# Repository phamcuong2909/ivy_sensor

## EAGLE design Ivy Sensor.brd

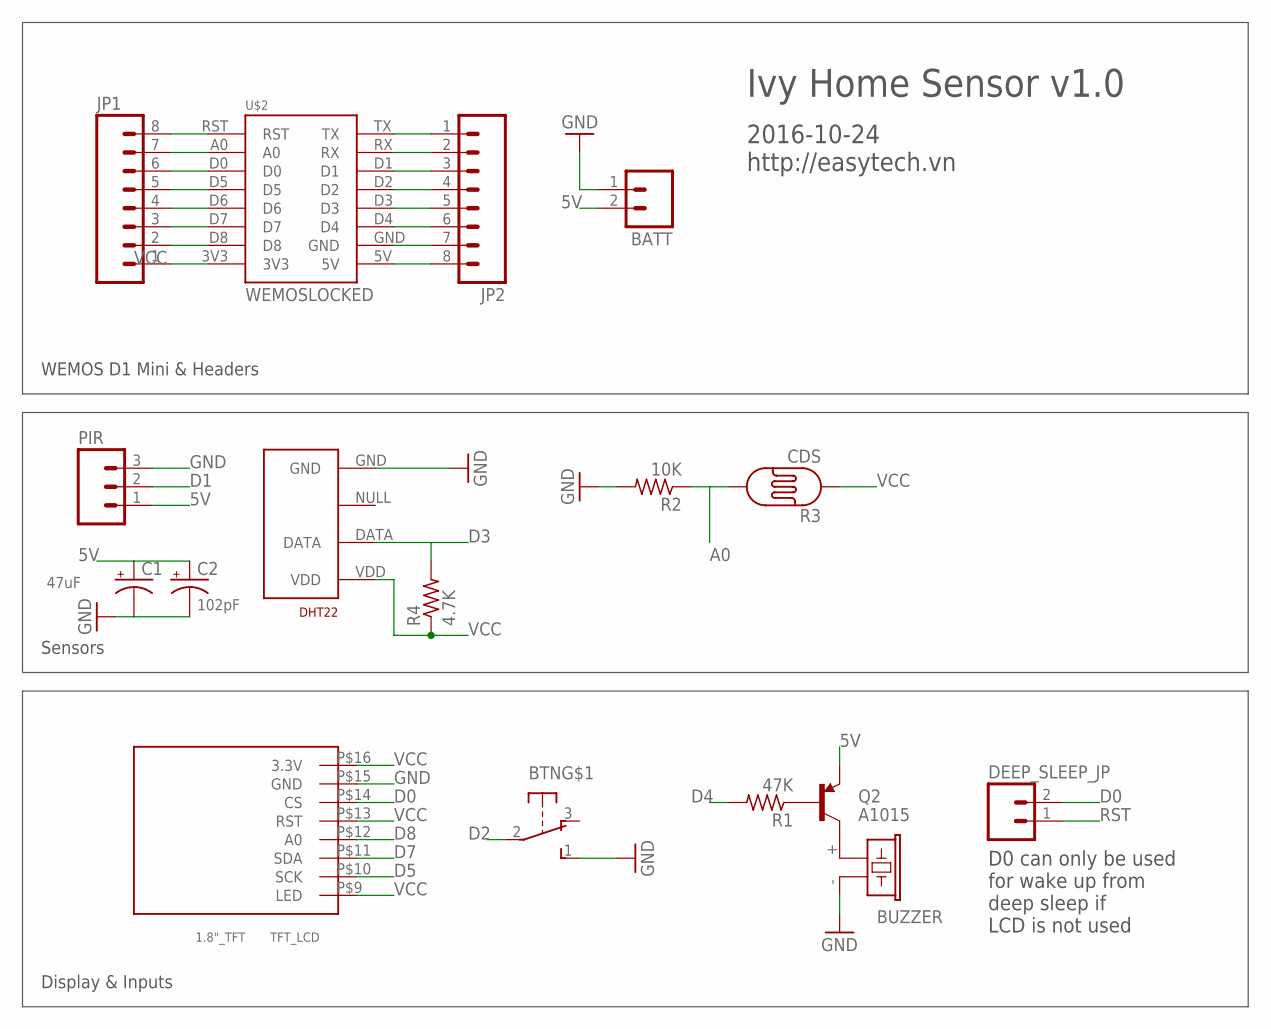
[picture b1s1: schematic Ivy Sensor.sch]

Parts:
BATT: M02PTH; 1X02
BTN: OS102011MA1Q
BUZZER: F/CM12P
C1: 47uF; CPOL-RADIAL-10UF-25V
C2: 102pF; CPOL-RADIAL-10UF-25V
DEEP_SLEEP_JP: M02PTH; 1X02
DHT22: RHT03_DHT-22_AM2302RA; RHT03_DHT-22/RA
JP1, JP2: M08; 1X08_ROUND
PIR: M03PTH; 1X03
Q2: A1015; SOT23-3
R1: 47K; R0805
R2: 10K; R0805
R3: CDS; PHOTOCELL_THIN
R4: 4.7K; R0805
TFT_LCD: 1.8"_TFT
U$2: WEMOSLOCKED; WEMOS_LOCKED

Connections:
5V: BATT.2, C1.1 (+), C2.1 (+), JP2.8, PIR.1, Q2.2 (E), U$2.5V
A0: JP1.7, R2.1, R3.2, U$2.A0
D0: DEEP_SLEEP_JP.2, JP1.6, TFT_LCD.P$14 (CS), U$2.D0
D1: JP2.3, PIR.2, U$2.D1
D2: BTN.2, JP2.4, U$2.D2
D3: DHT22.DATA, JP2.5, R4.2, U$2.D3
D4: JP2.6, R1.2, U$2.D4
D5: JP1.5, TFT_LCD.P$10 (SCK), U$2.D5
D6: JP1.4, U$2.D6
D7: JP1.3, TFT_LCD.P$11 (SDA), U$2.D7
D8: JP1.2, TFT_LCD.P$12 (A0), U$2.D8
GND: BATT.1, BTN.1 (S), BUZZER.- (2), C1.2 (-), C2.2 (-), DHT22.GND, JP2.7, PIR.3, R2.2, TFT_LCD.P$15 (GND), U$2.GND
RST: DEEP_SLEEP_JP.1, JP1.8, U$2.RST
RX: JP2.2, U$2.RX
TX: JP2.1, U$2.TX
T_B: Q2.1 (B), R1.1
T_C: BUZZER.+ (1), Q2.3 (C)
VCC: DHT22.VDD, JP1.1, R3.1, R4.1, TFT_LCD.P$9 (LED), TFT_LCD.P$13 (RST), TFT_LCD.P$16 (3.3V), U$2.3V3

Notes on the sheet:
Ivy Home Sensor v1.0
2016-10-24 http://easytech.vn
WEMOS D1 Mini & Headers
Sensors
Display & Inputs
D0 can only be used for wake up from deep sleep if LCD is not used

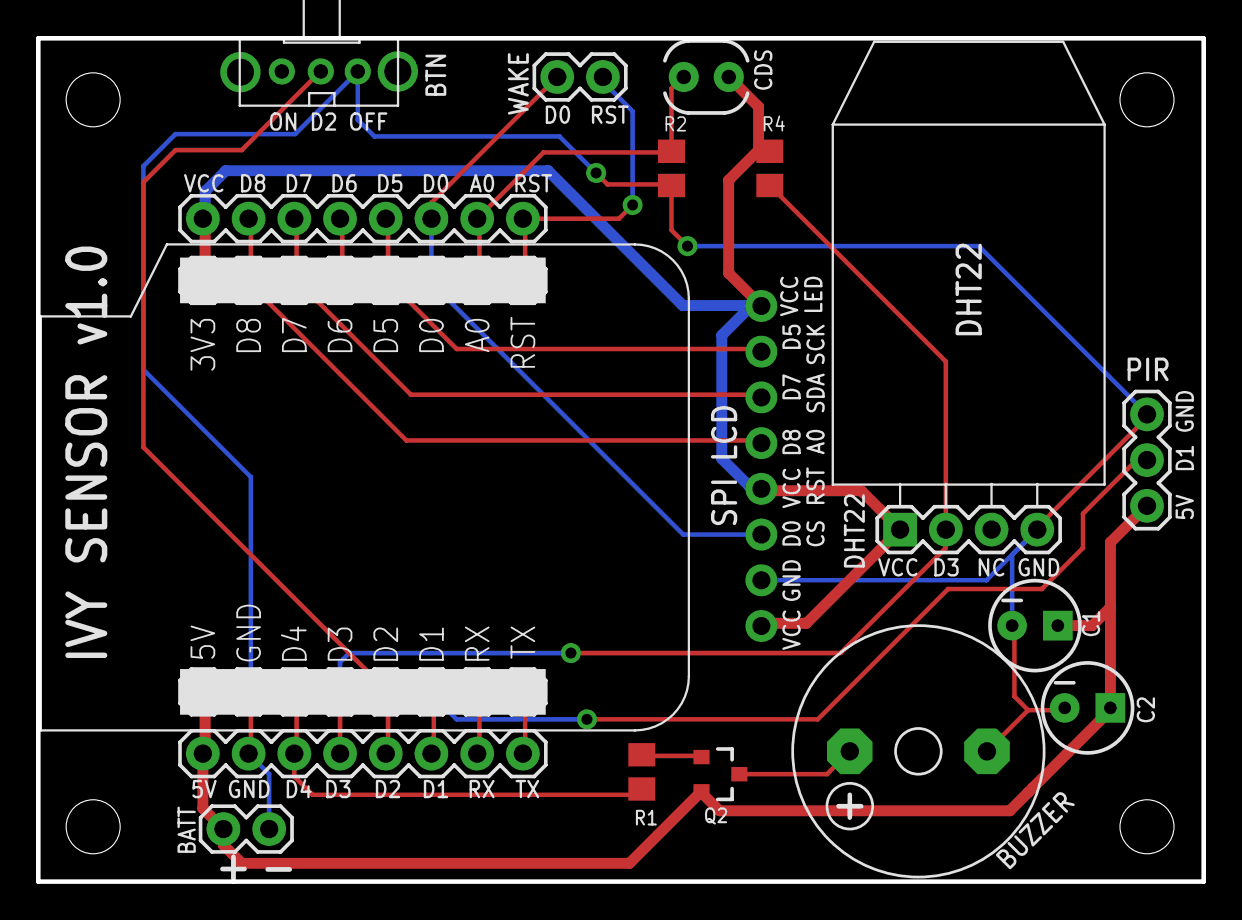
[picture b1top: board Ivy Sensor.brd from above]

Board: 2 copper layers, 64.7 x 46.9 mm, 21 parts (1 on the bottom side), 18 nets.

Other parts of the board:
U$6, U$7, U$8, U$9: KFH-M3

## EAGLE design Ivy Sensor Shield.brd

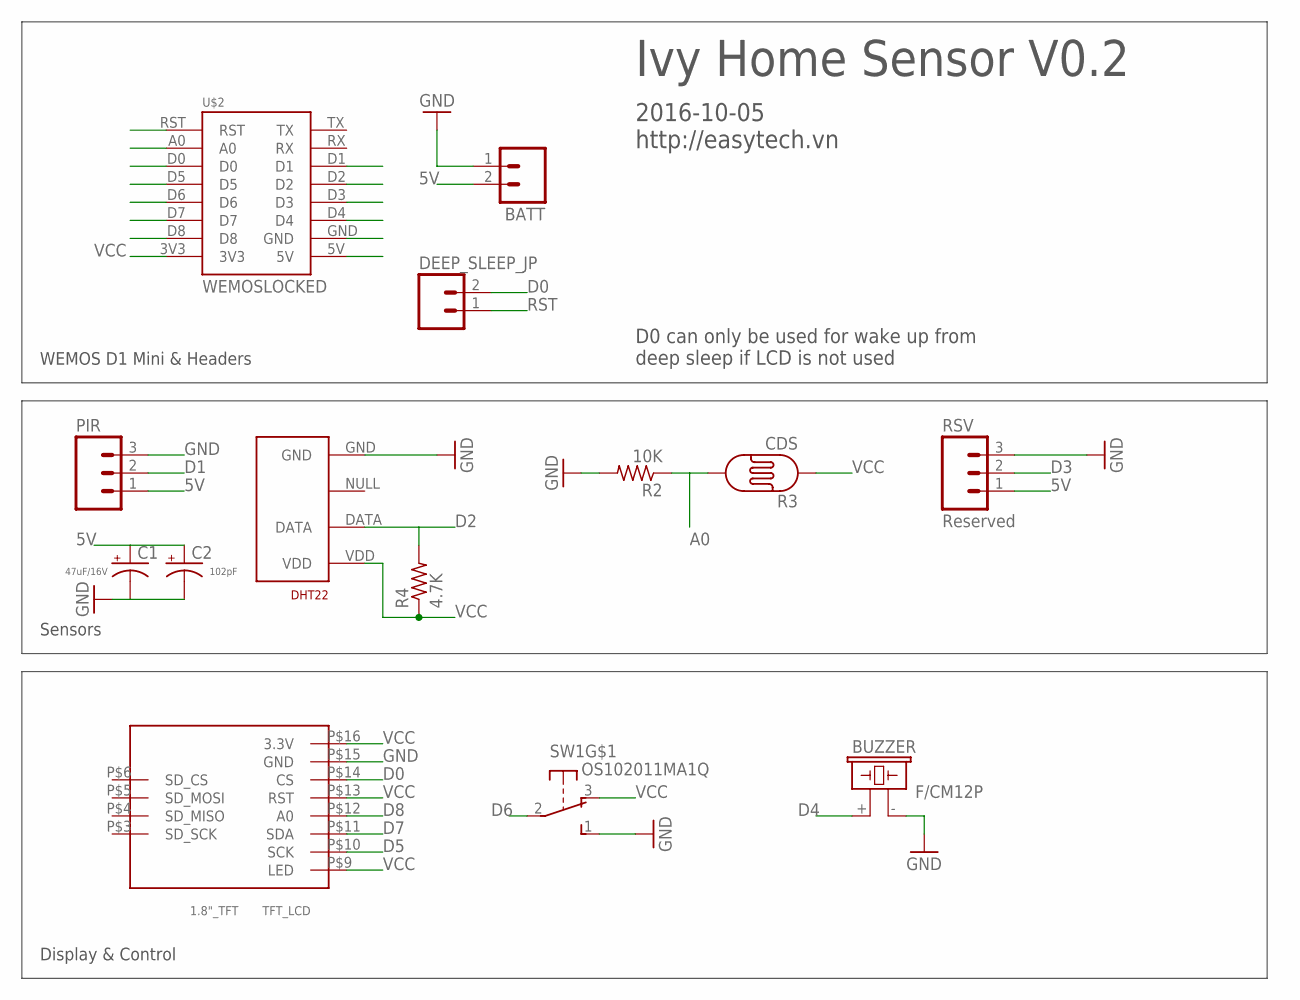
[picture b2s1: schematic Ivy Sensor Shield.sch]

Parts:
BATT: M02PTH; 1X02
BUZZER: F/CM12P
C1: 47uF/16V; CPOL-RADIAL-10UF-25V
C2: 102pF; CPOL-RADIAL-10UF-25V
DEEP_SLEEP_JP: M02PTH; 1X02
DHT22: RHT03_DHT-22_AM2302RA; RHT03_DHT-22/RA
PIR: M03PTH; 1X03
R2: 10K; R0805
R3: CDS; PHOTOCELL_THIN
R4: 4.7K; R0805
RSV: Reserved; 1X03
SW1: OS102011MA1Q
TFT_LCD: 1.8"_TFT
U$2: WEMOSLOCKED; WEMOS_LOCKED

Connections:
5V: BATT.2, C1.1 (+), C2.1 (+), PIR.1, RSV.1, U$2.5V
A0: R2.1, R3.2, U$2.A0
D0: DEEP_SLEEP_JP.2, TFT_LCD.P$14 (CS), U$2.D0
D1: PIR.2, U$2.D1
D2: DHT22.DATA, R4.2, U$2.D2
D3: RSV.2, U$2.D3
D4: BUZZER.+ (1), U$2.D4
D5: TFT_LCD.P$10 (SCK), U$2.D5
D6: SW1.2, U$2.D6
D7: TFT_LCD.P$11 (SDA), U$2.D7
D8: TFT_LCD.P$12 (A0), U$2.D8
GND: BATT.1, BUZZER.- (2), C1.2 (-), C2.2 (-), DHT22.GND, PIR.3, R2.2, RSV.3, SW1.1 (S), TFT_LCD.P$15 (GND), U$2.GND
RST: DEEP_SLEEP_JP.1, U$2.RST
VCC: DHT22.VDD, R3.1, R4.1, SW1.3 (O), TFT_LCD.P$9 (LED), TFT_LCD.P$13 (RST), TFT_LCD.P$16 (3.3V), U$2.3V3

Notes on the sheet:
Ivy Home Sensor V0.2
2016-10-05 http://easytech.vn
WEMOS D1 Mini & Headers
Sensors
Display & Control
D0 can only be used for wake up from deep sleep if LCD is not used

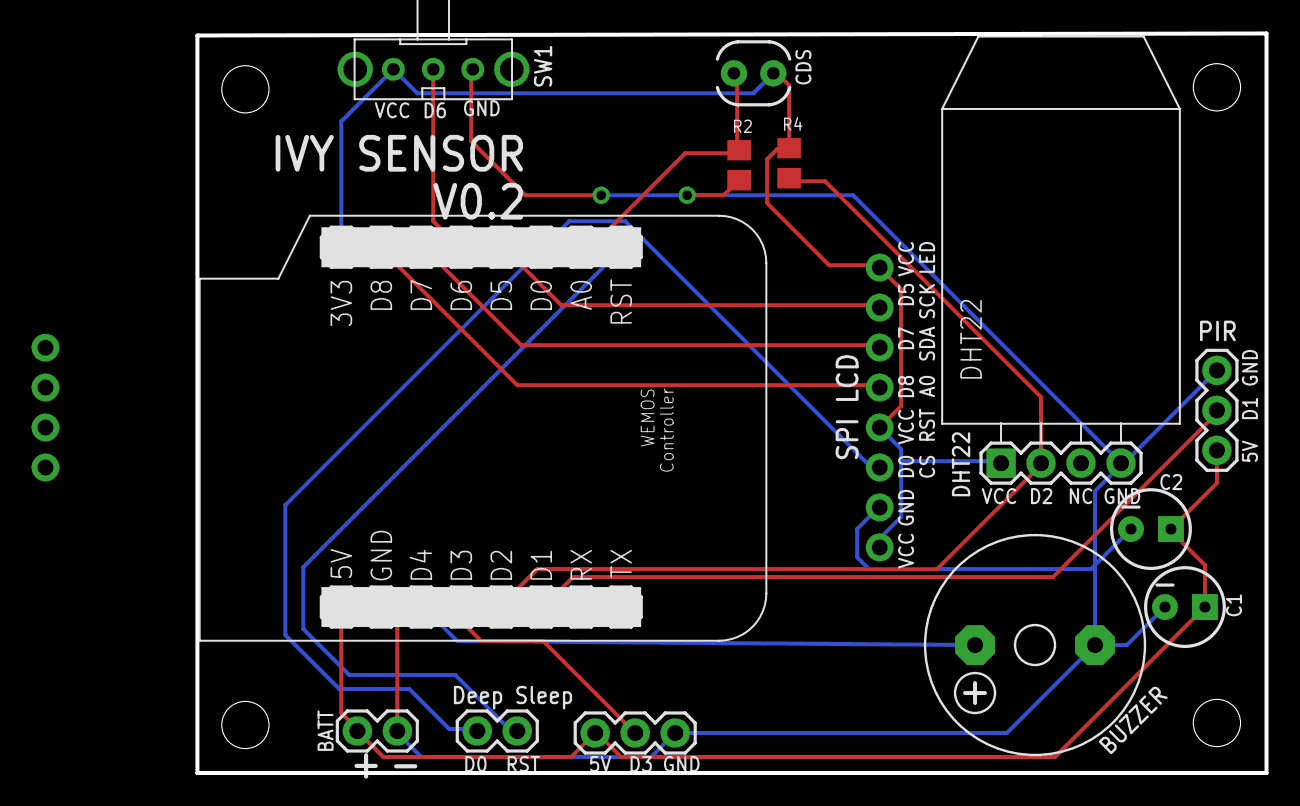
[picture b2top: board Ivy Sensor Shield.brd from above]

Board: 2 copper layers, 67.9 x 47.0 mm, 18 parts (1 on the bottom side), 14 nets.

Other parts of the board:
U$6, U$7, U$8, U$9: KFH-M3

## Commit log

2016-06-09 Add Eagle and laser cut design files
2016-06-09 Add schematic picture
2016-06-10 Update box design to be corner rounded
2016-06-13 Add sample code for using with Oled and DHT22
2016-06-15 Add sample code for oled and ds18b20
2016-06-15 Update box design
2016-09-06 Add design for box and new code
2016-09-25 Update sample code
2016-09-25 Remove obsolete sample code
2016-10-30 Update design to remove pad outside board outline

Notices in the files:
parts and their libraries:
penn-engineering: Copyright (C) 2010, Bob Starr
SparkFun-Connectors: Licensing: Creative Commons ShareAlike 4.0 International - https://creativecommons.org/licenses/by-sa/4.0
SparkFun: Licensing: CC v3.0 Share-Alike You are welcome to use this library for commercial purposes.
